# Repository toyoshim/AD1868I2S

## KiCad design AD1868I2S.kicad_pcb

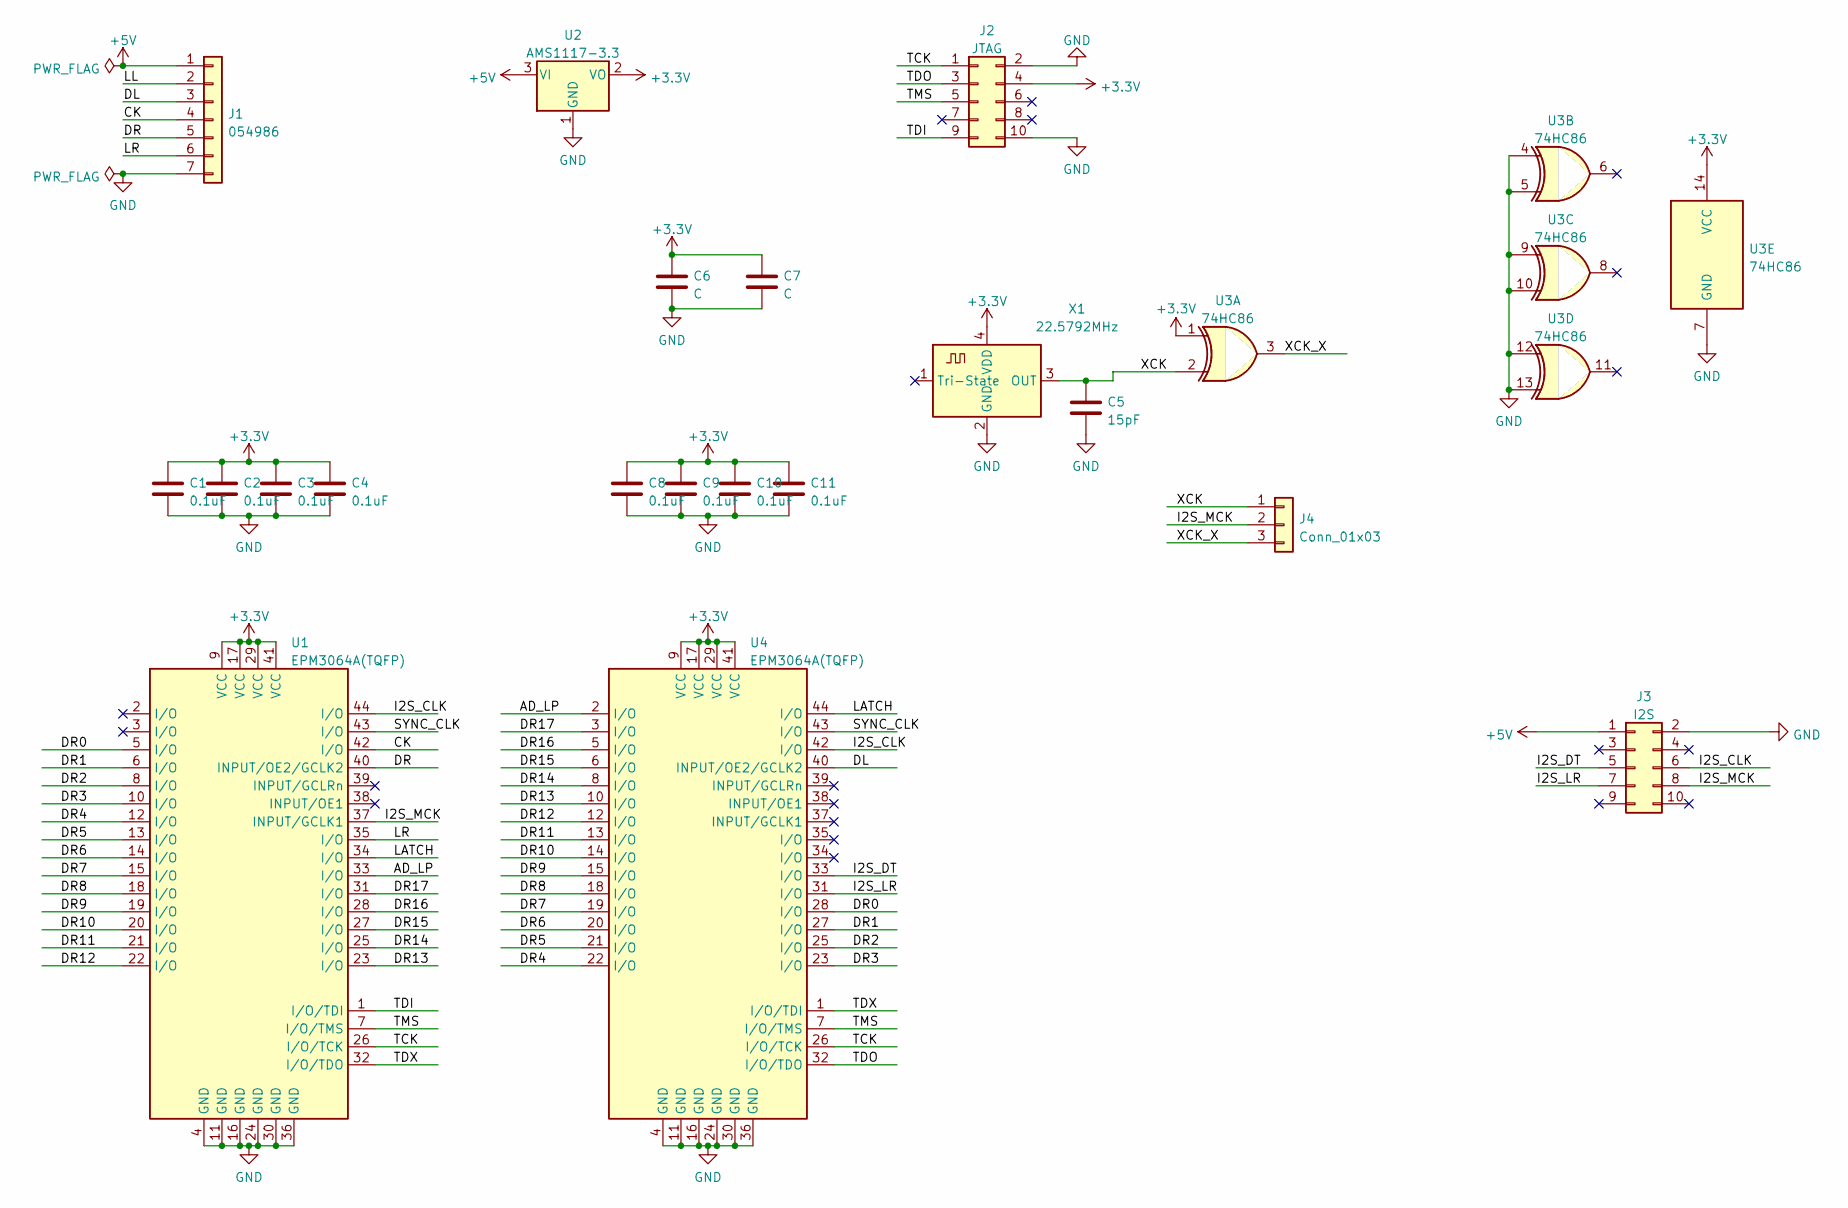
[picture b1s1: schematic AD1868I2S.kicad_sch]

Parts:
C1, C2, C3, C4, C8, C9, C10, C11: 0.1uF; C_0603_1608Metric_Pad1.08x0.95mm_HandSolder
C5: 15pF; C_0603_1608Metric_Pad1.08x0.95mm_HandSolder
C6, C7: C; C_0603_1608Metric_Pad1.08x0.95mm_HandSolder
J1: 054986; PinHeader_1x07_P2.54mm_Vertical
J2: JTAG; PinHeader_2x05_P2.54mm_Vertical
J3: I2S; PinHeader_2x05_P2.54mm_Vertical
J4: Conn_01x03; SolderJumper-3_P1.3mm_Open_Pad1.0x1.5mm
U1, U4: EPM3064A(TQFP); TQFP-44_10x10mm_P0.8mm
U2: AMS1117-3.3; SOT-223-3_TabPin2
U3: 74HC86; SOIC-14_3.9x8.7mm_P1.27mm
X1: 22.5792MHz; SMD_OSC_3.2x2.5

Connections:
+3.3V: C1.1, C2.1, C3.1, C4.1, C6.1, C7.1, C8.1, C9.1, C10.1, C11.1, J2.4, U1.9 (VCC), U1.17 (VCC), U1.29 (VCC), U1.41 (VCC), U2.2 (VO), U3.1, U3.14 (VCC), U4.9 (VCC), U4.17 (VCC), U4.29 (VCC), U4.41 (VCC), X1.4 (VDD)
+5V: J1.1, J3.1, U2.3 (VI)
/AD_LP: U1.33 (I/O), U4.2 (I/O)
/CK: J1.4, U1.42 (I/O)
/DL: J1.3, U4.40 (INPUT/OE2/GCLK2)
/DR: J1.5, U1.40 (INPUT/OE2/GCLK2)
/DR0: U1.5 (I/O), U4.28 (I/O)
/DR1: U1.6 (I/O), U4.27 (I/O)
/DR2: U1.8 (I/O), U4.25 (I/O)
/DR3: U1.10 (I/O), U4.23 (I/O)
/DR4: U1.12 (I/O), U4.22 (I/O)
/DR5: U1.13 (I/O), U4.21 (I/O)
/DR6: U1.14 (I/O), U4.20 (I/O)
/DR7: U1.15 (I/O), U4.19 (I/O)
/DR8: U1.18 (I/O), U4.18 (I/O)
/DR9: U1.19 (I/O), U4.15 (I/O)
/DR10: U1.20 (I/O), U4.14 (I/O)
/DR11: U1.21 (I/O), U4.13 (I/O)
/DR12: U1.22 (I/O), U4.12 (I/O)
/DR13: U1.23 (I/O), U4.10 (I/O)
/DR14: U1.25 (I/O), U4.8 (I/O)
/DR15: U1.27 (I/O), U4.6 (I/O)
/DR16: U1.28 (I/O), U4.5 (I/O)
/DR17: U1.31 (I/O), U4.3 (I/O)
/I2S_CLK: J3.6, U1.44 (I/O), U4.42 (I/O)
/I2S_DT: J3.5, U4.33 (I/O)
/I2S_LR: J3.7, U4.31 (I/O)
/I2S_MCK: J3.8, J4.2, U1.37 (INPUT/GCLK1)
/LATCH: U1.34 (I/O), U4.44 (I/O)
/LL: J1.2
/LR: J1.6, U1.35 (I/O)
/SYNC_CLK: U1.43 (I/O), U4.43 (I/O)
/TCK: J2.1, U1.26 (I/O/TCK), U4.26 (I/O/TCK)
/TDI: J2.9, U1.1 (I/O/TDI)
/TDO: J2.3, U4.32 (I/O/TDO)
/TDX: U1.32 (I/O/TDO), U4.1 (I/O/TDI)
/TMS: J2.5, U1.7 (I/O/TMS), U4.7 (I/O/TMS)
/XCK: C5.1, J4.1, U3.2, X1.3 (OUT)
/XCK_X: J4.3, U3.3
GND: C1.2, C2.2, C3.2, C4.2, C5.2, C6.2, C7.2, C8.2, C9.2, C10.2, C11.2, J1.7, J2.2, J2.10, J3.2, U1.4 (GND), U1.11 (GND), U1.16 (GND), U1.24 (GND), U1.30 (GND), U1.36 (GND), U2.1 (GND), U3.4, U3.5, U3.7 (GND), U3.9, U3.10, U3.12, U3.13, U4.4 (GND), U4.11 (GND), U4.16 (GND), U4.24 (GND), U4.30 (GND), U4.36 (GND), X1.2 (GND)

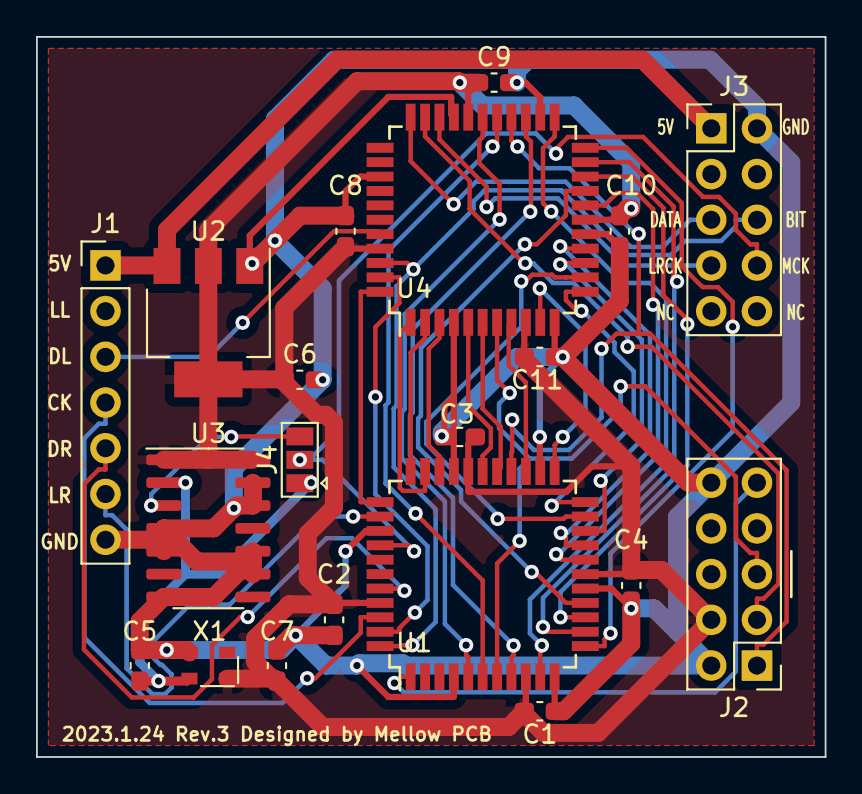
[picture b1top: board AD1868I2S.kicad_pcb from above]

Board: 2 copper layers, 43.8 x 40.0 mm, 20 parts (0 on the bottom side), 39 nets.

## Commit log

2023-01-22 rev1
2023-01-23 update pcb to rev2
2023-02-05 initial logic
    this doesn't work well as reading updating value may have a big gap
    for the final value, and it results in noise.
2023-02-05 working epm3128 version
2023-02-06 add a test bench for SampleLatch
2023-02-06 add test for I2sEnmcoder
2023-02-06 rev3
